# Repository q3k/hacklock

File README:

This is the Hackerspace Warsaw electronic lock mk2 project.

Work in progress! This is a prototype for a TP-Link WR703n based hardware
solution - with a I2C bus on which there is a MAX7300 IO expander and a PN532
NFC tag reader. The I2C is software bit-banged by the kernel, drivers for both
the IO expander and the PN532 are written in Lua.

Files:
    hslockmk2/                                    - this directory
             software/
                      main/                       - code for the central unit of the lock
                           main.lua               - main Lua script
                           lua-libs/              - other Lua libraries
                                   mips-bin/      - C libraries compiled for MIPS/OpenWRT
                                   luai2c.tar.gz  - C i2c library source
                                   luasha2.tar.gz - C sha2 library source

                      keypad/                     - AVR code for the keypad               
             hardware/
                     keypad/                      - KiCAD files for the keypad PCB

You will additonally need luasec, luaposix and luasocket. But you can easily
find these in your favourite distribution, or even the OpenWRT source tree.

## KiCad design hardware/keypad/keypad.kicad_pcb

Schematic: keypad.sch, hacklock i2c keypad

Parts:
BZ1: BUZZER
C1, C2, C3: 100n
C4, C5: 22p
I1: ATMEGA8
J1, J2: HEADER_6
J3: ISP
J4: I2C
LD1: GREEN
LD2: RED
R3, R4: 40k
R5, R6: 220
SW1: SW_PUSH
X1: CRYSTAL

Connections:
+5V: C1.2, C2.2, C3.2, I1.4 (VCC), I1.6 (VCC), I1.18 (AVCC), J3.2, J4.1, R3.1, SW1.2
GND: BZ1.2, C1.1, C2.1, C3.1, C4.2, C5.2, I1.3 (GND), I1.5 (GND), I1.21 (GND), J3.6, J4.4, R4.2, R5.2, R6.2
unnamed: I1.31 (PD1(TXD)), J1.3
unnamed: I1.2 (PD4(XCK/T0)), J2.6
unnamed: I1.9 (PD5(T1)), J2.5
unnamed: I1.10 (PD6(AIN0)), J2.4
unnamed: I1.11 (PD7(AIN1)), J2.3
unnamed: I1.30 (PD0(RXD)), J1.4
unnamed: I1.32 (PD2(INT0)), J1.2
unnamed: I1.1 (PD3(INT1)), J1.1
unnamed: I1.23 (PC0(ADC0)), LD1.1 (A)
unnamed: I1.24 (PC1(ADC1)), LD2.1 (A)
unnamed: LD1.2 (K), R5.1
unnamed: LD2.2 (K), R6.1
unnamed: BZ1.1, I1.25 (PC2(ADC2))
unnamed: I1.26 (PC3(ADC3)), R4.1, SW1.1
unnamed: C5.1, I1.8 (PB7(XTAL2/TOSC2)), X1.1
unnamed: C4.1, I1.7 (PB6(XTAL1/TOSC1)), X1.2
unnamed: I1.16 (PB4(MISO)), J3.1
unnamed: I1.17 (PB5(SCK)), J3.3
unnamed: I1.29 (PC6(RESET-)), J3.5, R3.2
unnamed: I1.15 (PB3(MOSI/OC2)), J3.4
unnamed: I1.27 (PC4(ADC4/SDA)), J4.2
unnamed: I1.28 (PC5(ADC5/SCL)), J4.3

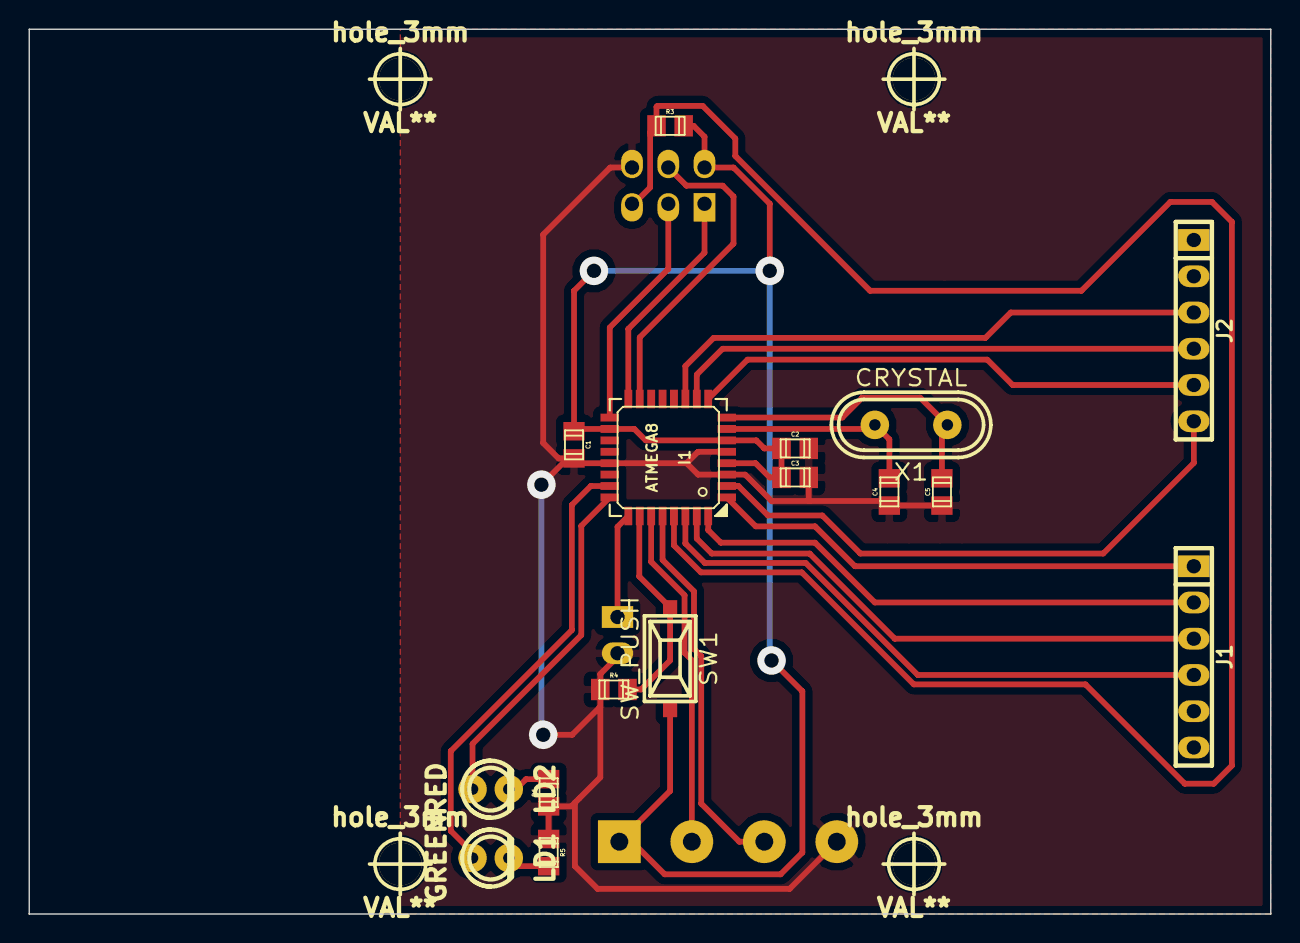
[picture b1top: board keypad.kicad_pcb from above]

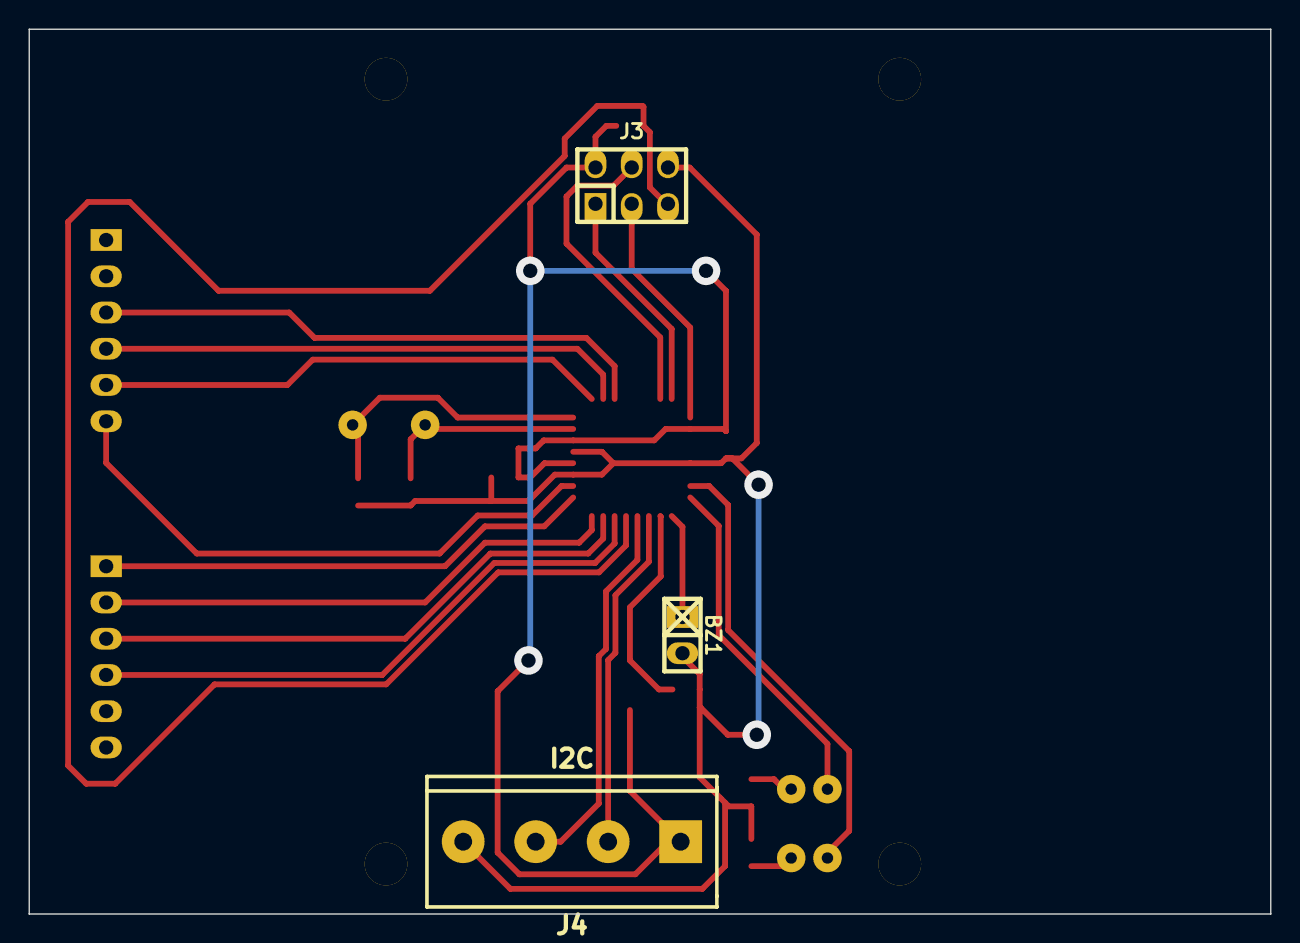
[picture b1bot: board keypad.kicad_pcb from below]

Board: 2 copper layers, 87.0 x 62.0 mm, 23 parts (3 on the bottom side), 24 nets.

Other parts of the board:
hole_3mm, hole_3mm#2, hole_3mm#3, hole_3mm#4: VAL**; hole_3mm

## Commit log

2013-09-05 Initial commit of test/ugly/prototype code.
2013-09-06 Massive refactor of source code.
2013-09-06 Updated license.
2013-09-14 First revision of keypad schematic.
2013-09-15 First revision of keypad PCB.
    http://i.imgur.com/pNjvT0o.jpg
2013-09-15 Changed directory structure.
2013-09-15 First test of keypad software - the LEDs work.
2013-09-15 Keypad hardware manufacturing changes.
2013-09-15 Buzzer code.
2013-09-15 Debug LEDs and Buzzer on start.
2013-09-17 Updated README.
2013-09-17 Keypad support for the keypad. Woo!
